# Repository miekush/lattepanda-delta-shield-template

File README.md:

# LattePanda Delta Shield KiCad Template
KiCad Project Template for LattePanda Delta Shields

# PCB

# Schematic

Designed by Mike Kushnerik (miekush) in KiCad V6

# License

MKE supports the open source hardware community by sharing hardware design files freely on GitHub!

Please support MKE by purchasing products on [Tindie](https://www.tindie.com/stores/mkengineering/)!

Designed by Mike Kushnerik (miekush)

Licensed under [Creative Commons Attribution-ShareAlike CC BY-SA 4.0](http://creativecommons.org/licenses/by-sa/4.0/)

All text above must be included in any redistribution!

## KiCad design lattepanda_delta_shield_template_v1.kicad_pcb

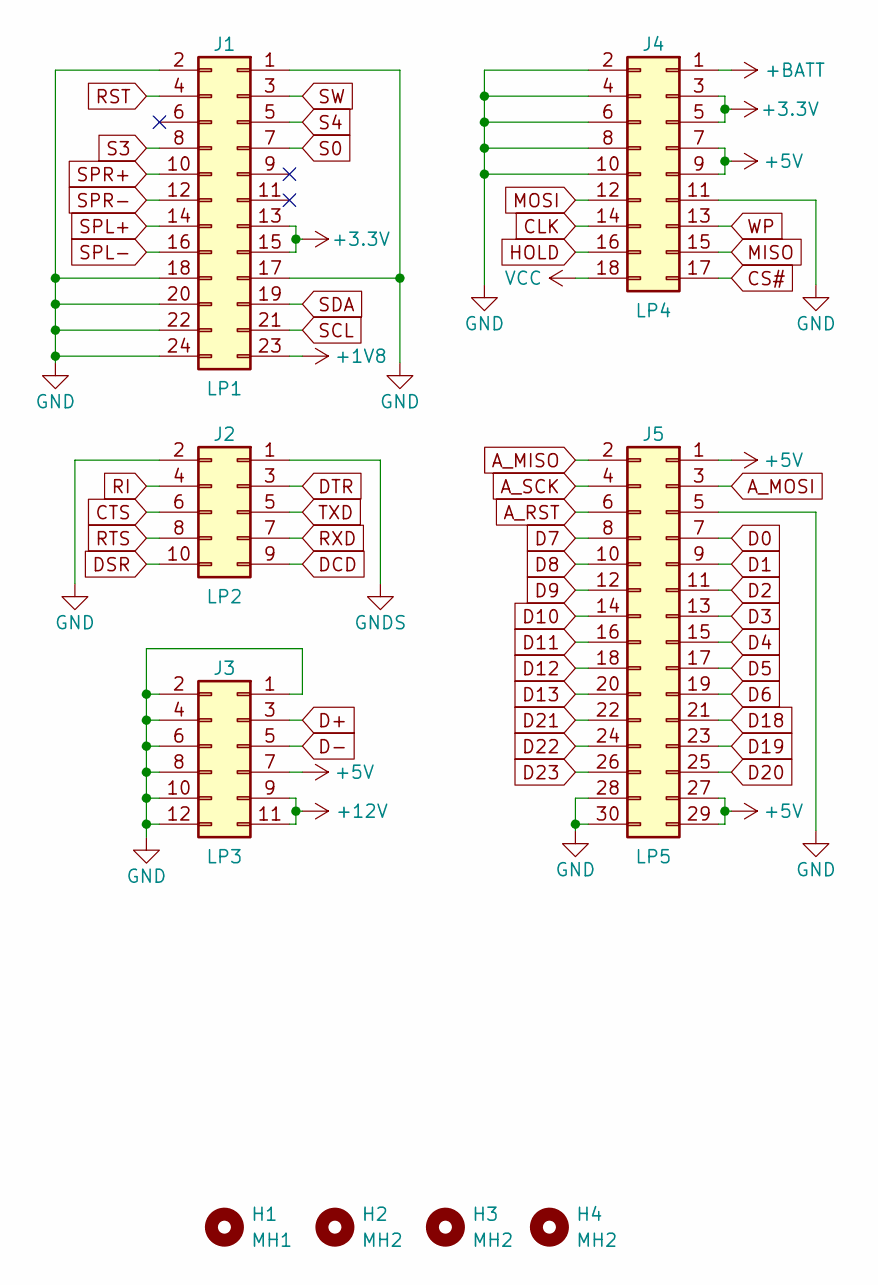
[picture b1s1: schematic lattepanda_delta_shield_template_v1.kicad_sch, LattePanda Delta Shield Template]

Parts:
H1: MH1; MountingHole_3.5mm
H2, H3, H4: MH2; MountingHole_3.5mm
J1: LP1; PinHeader_2x12_P2.54mm_Vertical
J2: LP2; PinHeader_2x05_P2.54mm_Vertical
J3: LP3; PinHeader_2x06_P2.54mm_Vertical
J4: LP4; PinHeader_2x09_P2.54mm_Vertical
J5: LP5; PinHeader_2x15_P2.54mm_Vertical

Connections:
+1V8: J1.23
+3V3: J1.13, J1.15, J4.3, J4.5
+5V: J3.7, J4.7, J4.9, J5.1, J5.27, J5.29
+12V: J3.9, J3.11
+BATT: J4.1
A_MISO: J5.2
A_MOSI: J5.3
A_RST: J5.6
A_SCK: J5.4
CLK: J4.14
CS#: J4.17
CTS: J2.6
D0: J5.7
D1: J5.9
D2: J5.11
D3: J5.13
D4: J5.15
D5: J5.17
D6: J5.19
D7: J5.8
D8: J5.10
D9: J5.12
D10: J5.14
D11: J5.16
D12: J5.18
D13: J5.20
D18: J5.21
D19: J5.23
D20: J5.25
D21: J5.22
D22: J5.24
D23: J5.26
D+: J3.3
D-: J3.5
DCD: J2.9
DSR: J2.10
DTR: J2.3
GND: J1.1, J1.2, J1.17, J1.18, J1.20, J1.22, J1.24, J2.2, J3.1, J3.2, J3.4, J3.6, J3.8, J3.10, J3.12, J4.2, J4.4, J4.6, J4.8, J4.10, J4.11, J5.5, J5.28, J5.30
GNDS: J2.1
HOLD: J4.16
MISO: J4.15
MOSI: J4.12
RI: J2.4
RST: J1.4
RTS: J2.8
RXD: J2.7
S0: J1.7
S3: J1.8
S4: J1.5
SCL: J1.21
SDA: J1.19
SPL+: J1.14
SPL-: J1.16
SPR+: J1.10
SPR-: J1.12
SW: J1.3
TXD: J2.5
VCC: J4.18
WP: J4.13

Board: 2 copper layers, 9 parts (5 on the bottom side), 4 nets, no tracks yet.

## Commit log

2022-08-15 Initial upload
2022-08-15 Add image
2022-08-15 Add images

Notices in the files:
lattepanda_delta_shield_template_v1.kicad_sch:
https://creativecommons.org/licenses/by-sa/4.0
License: CC BY-SA 4.0
